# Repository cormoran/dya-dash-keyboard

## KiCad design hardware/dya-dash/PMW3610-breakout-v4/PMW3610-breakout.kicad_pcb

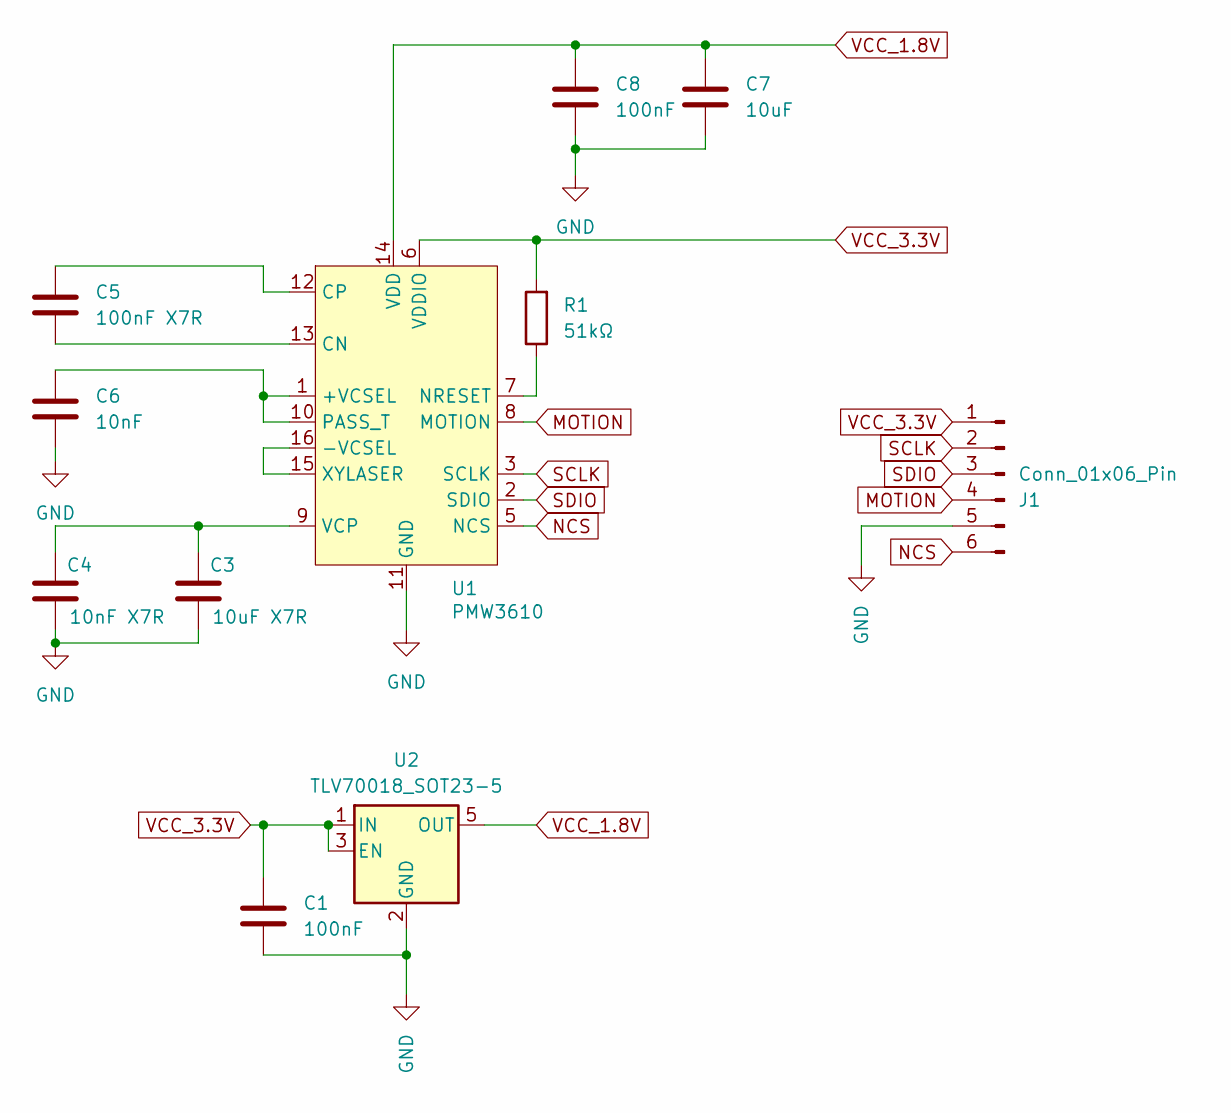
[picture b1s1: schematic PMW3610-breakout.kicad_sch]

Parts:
C1, C8: 100nF; C_0603_1608Metric; LCSC C14663
C3: 10uF X7R; C_0603_1608Metric; LCSC C19702
C4: 10nF X7R; C_0603_1608Metric; LCSC C57112
C5: 100nF X7R; C_0603_1608Metric; LCSC C14663
C6: 10nF; C_0603_1608Metric; LCSC C57112
C7: 10uF; C_0603_1608Metric; LCSC C19702
J1: Conn_01x06_Pin; JUSHUO-AFH34-S06FIA-1H; LCSC C5139821
R1: 51kΩ; R_0603_1608Metric; LCSC C23196
U1: PMW3610; PMW3610DM-SUDU 16Pin
U2: TLV70018_SOT23-5; SOT-23-5; LCSC C79924

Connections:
GND: C1.2, C3.2, C4.2, C6.2, C7.2, C8.2, J1.5, U1.11 (GND), U2.2 (GND)
MOTION: J1.4, U1.8 (MOTION)
NCS: J1.6, U1.5 (NCS)
unnamed: C6.1, U1.1 (+VCSEL), U1.10 (PASS_T)
unnamed: U1.15 (XYLASER), U1.16 (-VCSEL)
unnamed: C5.2, U1.13 (CN)
unnamed: C5.1, U1.12 (CP)
unnamed: R1.1, U1.7 (NRESET)
unnamed: C3.1, C4.1, U1.9 (VCP)
SCLK: J1.2, U1.3 (SCLK)
SDIO: J1.3, U1.2 (SDIO)
VCC_1.8V: C7.1, C8.1, U1.14 (VDD), U2.5 (OUT)
VCC_3.3V: C1.1, J1.1, R1.2, U1.6 (VDDIO), U2.1 (IN), U2.3 (EN)

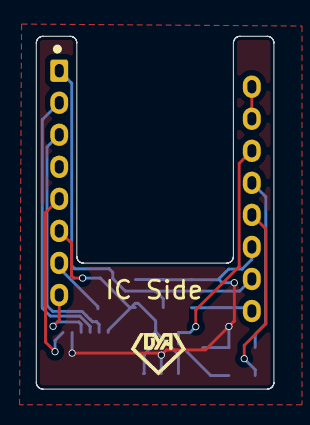
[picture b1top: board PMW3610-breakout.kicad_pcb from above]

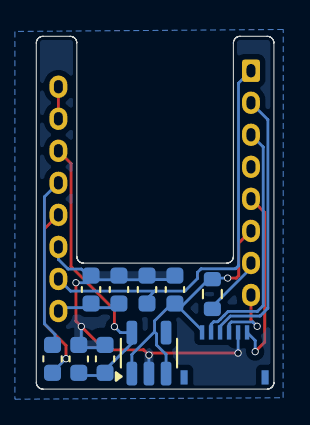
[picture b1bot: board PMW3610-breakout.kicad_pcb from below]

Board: 2 copper layers, 13.2 x 19.6 mm, 11 parts (10 on the bottom side), 13 nets.
